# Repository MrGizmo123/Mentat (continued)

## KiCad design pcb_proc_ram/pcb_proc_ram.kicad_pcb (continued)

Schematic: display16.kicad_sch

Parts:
C20, C21, C22: C; C_0805_2012Metric
D1, D2, D3, D4, D5, D6, D7, D8, D9, D10, D11, D12, D13, D14, D15, D16: LED; LED_Rectangular_W5.0mm_H2.0mm
R6, R7, R8, R9, R10, R11, R12, R13, R14, R15, R16, R17, R18, R19, R20, R21: R; R_0805_2012Metric
SW2: SW_SPDT; SW_E-Switch_EG1271_SPDT
U2, U19, U20: 74LS04; DIP-14_W7.62mm_Socket_LongPads

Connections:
/Display1/D1: U20.3; also elsewhere on the board
/Display/D0: U19.1; also elsewhere on the board
/Display/D1: U2.3; also elsewhere on the board
/Display/D2: U2.5; also elsewhere on the board
/Display/D3: U2.9; also elsewhere on the board
/Display/D4: U2.11; also elsewhere on the board
/Display/D5: U2.13; also elsewhere on the board
/Display/D6: U20.1; also elsewhere on the board
/Display/D7: U19.3; also elsewhere on the board
/Display/D8: U19.5; also elsewhere on the board
/Display/D9: U19.9; also elsewhere on the board
/Display/D10: U19.11; also elsewhere on the board
/Display/D11: U19.13; also elsewhere on the board
/Display/D12: U20.5; also elsewhere on the board
/Display/D13: U20.9; also elsewhere on the board
/Display/D14: U20.11; also elsewhere on the board
/Display/D15: U20.13; also elsewhere on the board
GND: C20.2, C21.2, C22.2, SW2.3 (C), U19.7 (GND), U20.7 (GND); also elsewhere on the board
unnamed: D1.2 (A), R6.1
unnamed: D1.1 (K), U19.2
unnamed: D2.2 (A), R7.1
unnamed: D2.1 (K), U2.4
unnamed: D3.2 (A), R8.1
unnamed: D3.1 (K), U2.6
unnamed: D4.2 (A), R9.1
unnamed: D4.1 (K), U2.8
unnamed: D5.2 (A), R10.1
unnamed: D5.1 (K), U2.10
unnamed: D6.2 (A), R11.1
unnamed: D6.1 (K), U2.12
unnamed: D7.2 (A), R12.1
unnamed: D7.1 (K), U20.2
unnamed: D8.2 (A), R13.1
unnamed: D8.1 (K), U19.4
unnamed: D9.2 (A), R14.1
unnamed: D9.1 (K), U19.6
unnamed: D10.2 (A), R15.1
unnamed: D10.1 (K), U19.8
unnamed: D11.2 (A), R16.1
unnamed: D11.1 (K), U19.10
unnamed: D12.2 (A), R17.1
unnamed: D12.1 (K), U19.12
unnamed: D13.2 (A), R18.1
unnamed: D13.1 (K), U20.6
unnamed: D14.2 (A), R19.1
unnamed: D14.1 (K), U20.8
unnamed: D15.2 (A), R20.1
unnamed: D15.1 (K), U20.10
unnamed: D16.2 (A), R21.1
unnamed: D16.1 (K), U20.12
unnamed 85: U20.4; also elsewhere on the board
unnamed: R6.2, R7.2, R8.2, R9.2, R10.2, R11.2, R12.2, R13.2, R14.2, R15.2, R16.2, R17.2, R18.2, R19.2, R20.2, R21.2, SW2.2 (B)
VCC: C20.1, C21.1, C22.1, SW2.1 (A), U19.14 (VCC), U20.14 (VCC); also elsewhere on the board

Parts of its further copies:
C23, C24, C25: C; C_0805_2012Metric
D17, D18, D19, D20, D21, D22, D23, D24, D25, D26, D27, D28, D29, D30, D31, D32: LED; LED_Rectangular_W5.0mm_H2.0mm
R22, R23, R24, R25, R26, R27, R28, R29, R30, R31, R32, R33, R34, R35, R36, R37: R; R_0805_2012Metric
SW3: SW_SPDT; SW_E-Switch_EG1271_SPDT
U21, U22: 74LS04; DIP-14_W7.62mm_Socket_LongPads

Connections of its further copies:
/Display1/D0: U21.1; also elsewhere on the board
/Display1/D2: U21.5; also elsewhere on the board
/Display1/D3: U21.9; also elsewhere on the board
/Display1/D4: U21.11; also elsewhere on the board
/Display1/D5: U21.13; also elsewhere on the board
/Display1/D6: U22.1; also elsewhere on the board
/Display1/D7: U21.3; also elsewhere on the board
/Display1/D8: U22.5; also elsewhere on the board
/Display1/D9: U22.9; also elsewhere on the board
/Display1/D10: U22.11; also elsewhere on the board
/Display1/D11: U22.13; also elsewhere on the board
GND: C23.2, C24.2, C25.2, SW3.3 (C), U22.7 (GND); also elsewhere on the board
unnamed: D17.2 (A), R22.1
unnamed: D17.1 (K), U21.2
unnamed: D18.2 (A), R23.1
unnamed 85: D18.1 (K); also elsewhere on the board
unnamed: D19.2 (A), R24.1
unnamed: D19.1 (K), U21.6
unnamed: D20.2 (A), R25.1
unnamed: D20.1 (K), U21.8
unnamed: D21.2 (A), R26.1
unnamed: D21.1 (K), U21.10
unnamed: D22.2 (A), R27.1
unnamed: D22.1 (K), U21.12
unnamed: D23.2 (A), R28.1
unnamed: D23.1 (K), U22.2
unnamed: D24.2 (A), R29.1
unnamed: D24.1 (K), U21.4
unnamed: D25.2 (A), R30.1
unnamed: D25.1 (K), U22.6
unnamed: D26.2 (A), R31.1
unnamed: D26.1 (K), U22.8
unnamed: D27.2 (A), R32.1
unnamed: D27.1 (K), U22.10
unnamed: D28.2 (A), R33.1
unnamed: D28.1 (K), U22.12
unnamed: D29.2 (A), R34.1
unnamed 107: D29.1 (K); also elsewhere on the board
unnamed: D30.2 (A), R35.1
unnamed 109: D30.1 (K); also elsewhere on the board
unnamed: D31.2 (A), R36.1
unnamed 111: D31.1 (K); also elsewhere on the board
unnamed: D32.2 (A), R37.1
unnamed 113: D32.1 (K); also elsewhere on the board
unnamed: R22.2, R23.2, R24.2, R25.2, R26.2, R27.2, R28.2, R29.2, R30.2, R31.2, R32.2, R33.2, R34.2, R35.2, R36.2, R37.2, SW3.2 (B)
VCC: C23.1, C24.1, C25.1, SW3.1 (A), U22.14 (VCC); also elsewhere on the board

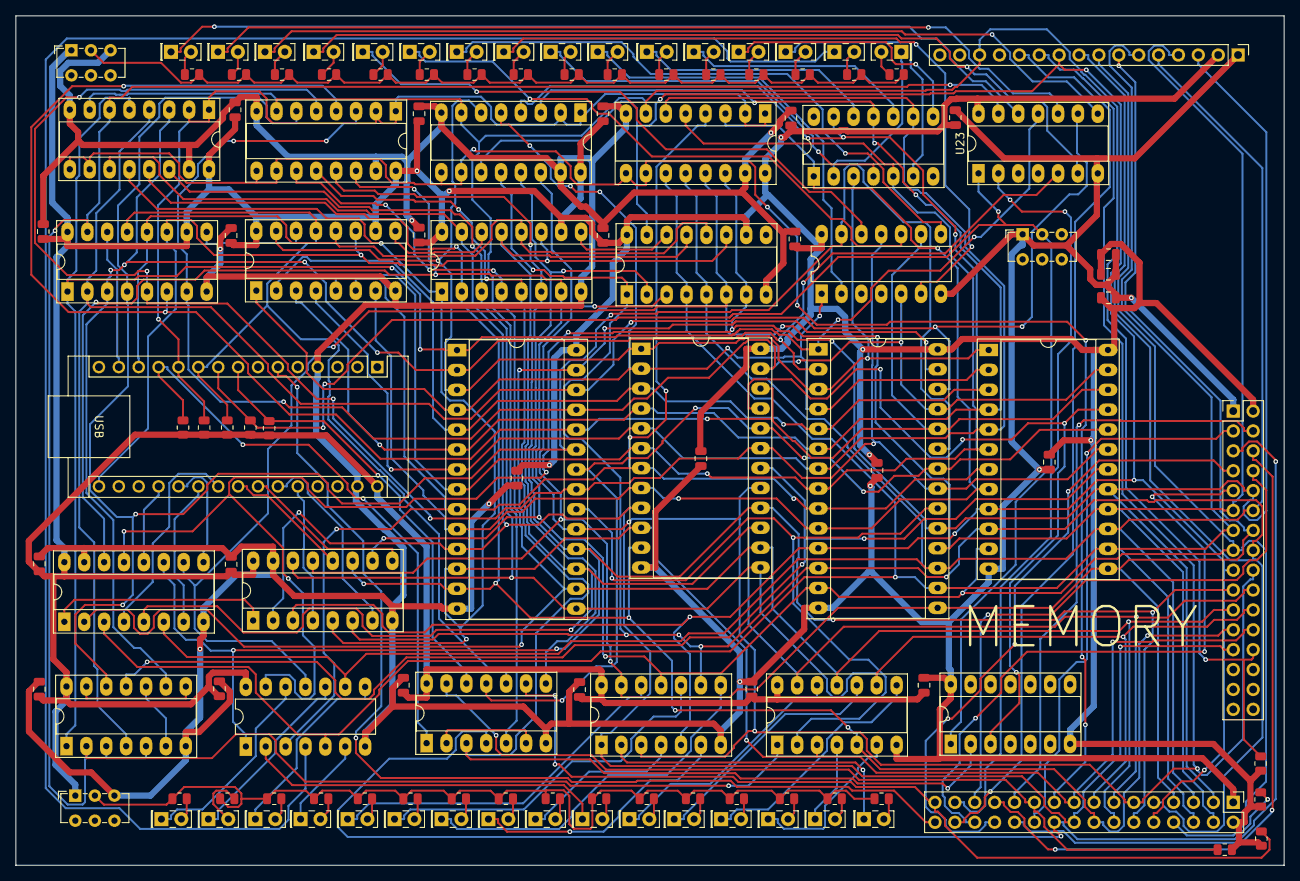
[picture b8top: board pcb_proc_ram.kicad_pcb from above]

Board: 2 copper layers, 162.0 x 108.5 mm, 128 parts (0 on the bottom side), 145 nets.

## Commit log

2024-09-14 Remove Backups
